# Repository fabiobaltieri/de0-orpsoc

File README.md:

DE0 ORPSoC
==========

This project is an addon I/O board for the Altera DE0-Nano.  It is meant to
be used as a development platform for the OpenRISC soft CPU.

The peripherals on the board are:

* Dual USB to UART
* RMII Ethernet
* SPI Ethernet
* RTC w/ battery backup (I2C)
* Thermal sensor (I2C)
* Micro SD card
* USB 1.1 Transceiver
* Reset button
* Status LEDs

All devices are powered at 3.3V from the DE0 regulators, though a set of
jumpers allow to power the DE0 itself from one of the USB ports of the I/O
board.

License
-------

This work is licensed under a Creative Commons Attribution-ShareAlike 3.0
License.

Contents
--------

    README      this file
    hardware/   source directory for the hardware design

Hardware
--------

All hardware files (schematic, layout and libraries) are in CadSoft Eagle
format.

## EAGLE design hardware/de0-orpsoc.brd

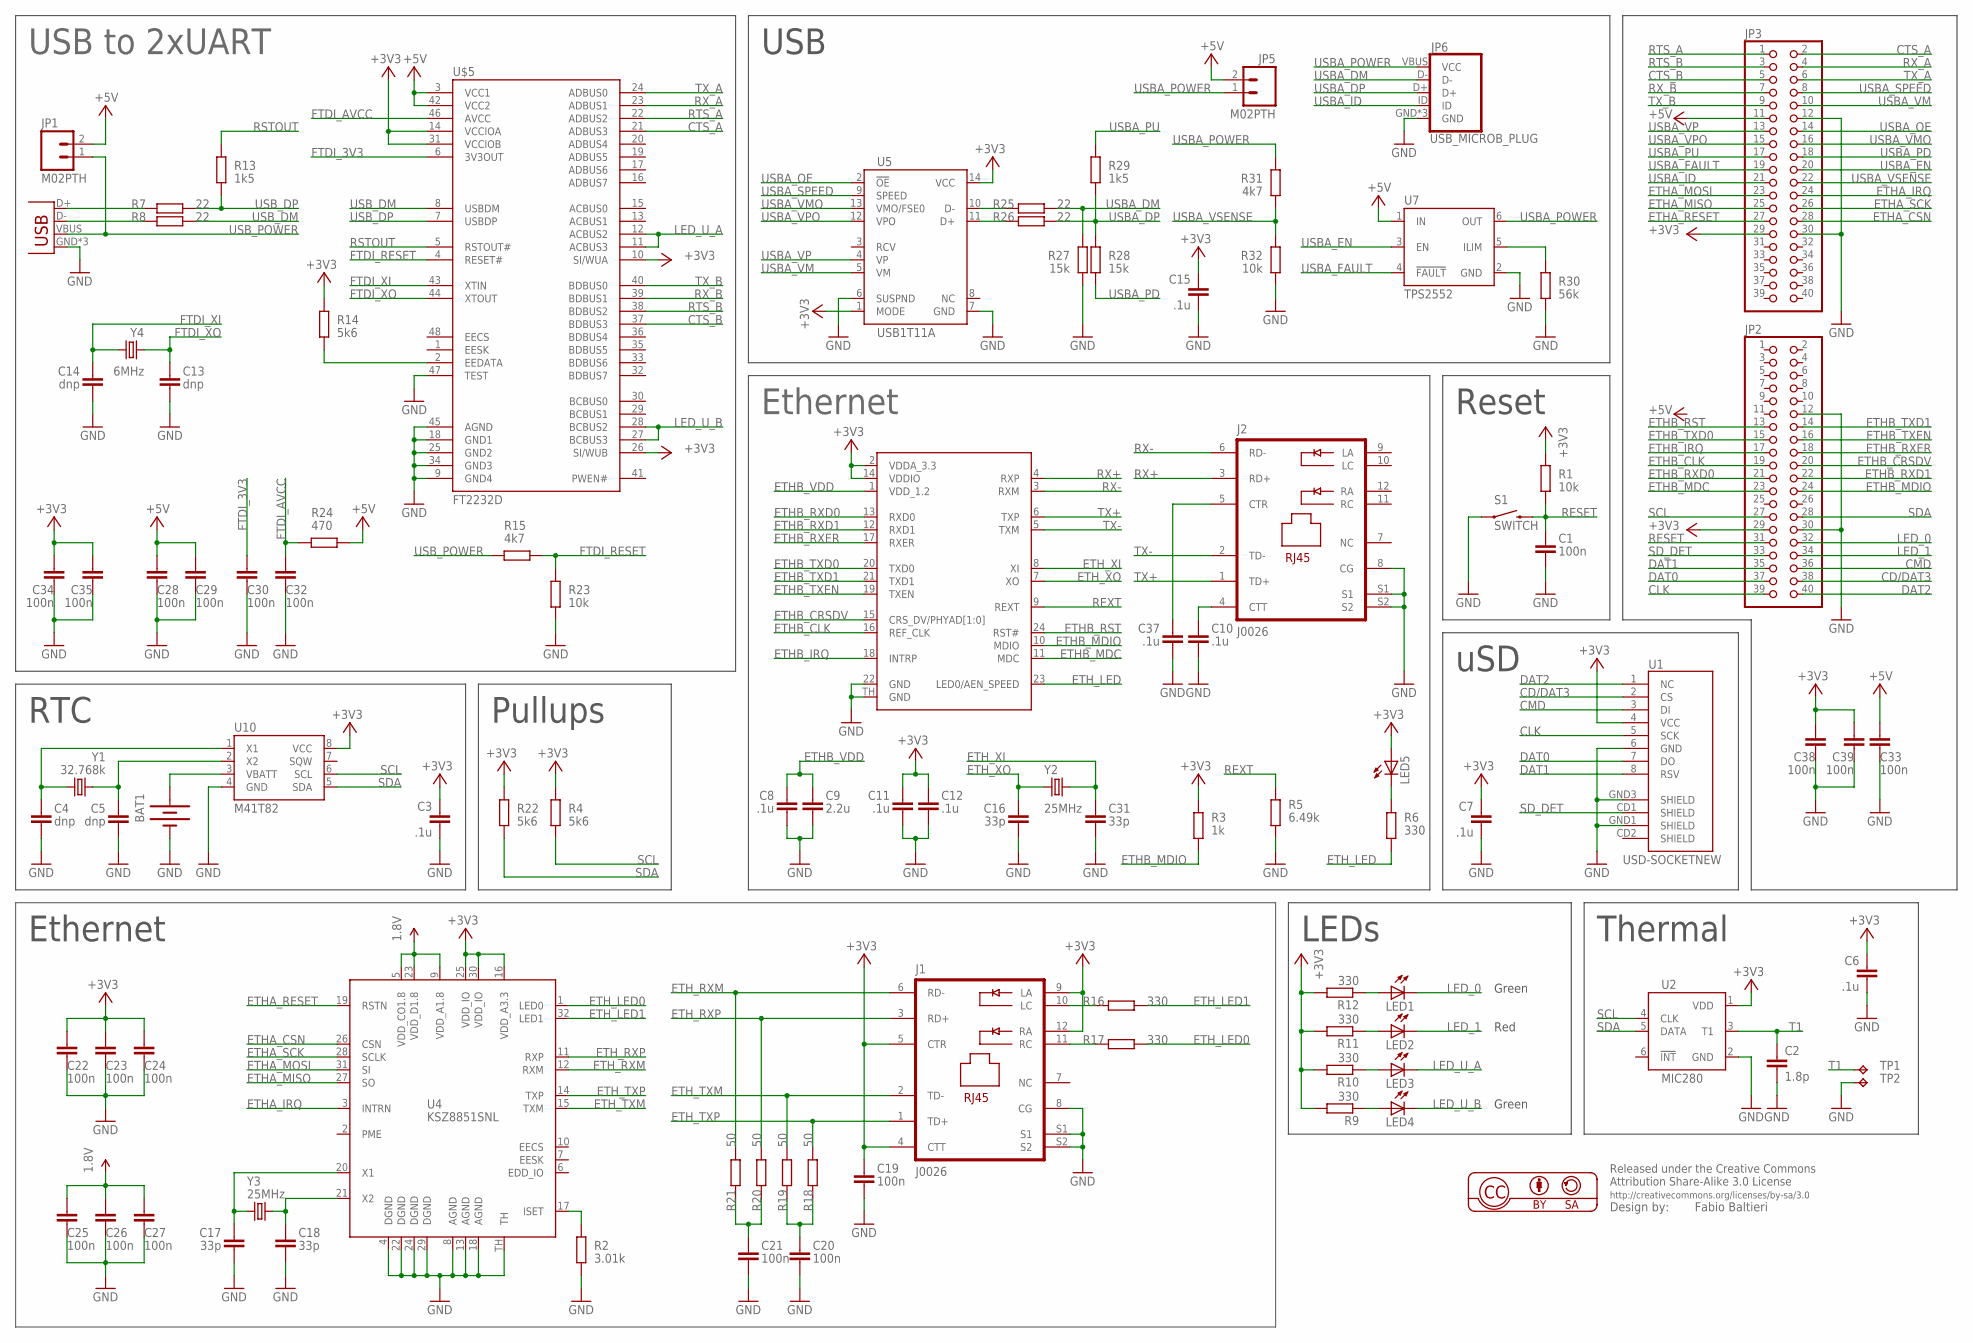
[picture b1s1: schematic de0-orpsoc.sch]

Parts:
BAT1: BATTERY12PTH; BATTCON_12MM_PTH
C1, C19, C20, C21, C22, C23, C24, C25, C26, C27, C28, C29, C30, C32, C33, C34, C35, C38, C39: 100n; C0603
C2: 1.8p; C0603
C3, C6, C7, C8, C10, C11, C12, C15, C37: .1u; C0603
C4, C5, C13, C14: dnp; C0603
C9: 2.2u; C0603
C16, C17, C18, C31: 33p; C0603
J1, J2: J0026; PJ-J0
JP1, JP5: M02PTH; 1X02
JP2, JP3: PINHD-2X20; 2X20
JP6: USB_MICROB_PLUG; USB-MICROB
JP10: USB-MICROB
LED1, LED2, LED3, LED4, LED5: LEDCHIPLED_0805; CHIPLED_0805
R1, R23, R32: 10k; R0603
R2: 3.01k; R0603
R3: 1k; R0603
R4, R14, R22: 5k6; R0603
R5: 6.49k; R0603
R6, R9, R10, R11, R12, R16, R17: 330; R0603
R7, R8, R25, R26: 22; R0603
R13, R29: 1k5; R0603
R15, R31: 4k7; R0603
R18, R19, R20, R21: 50; R0603
R24: 470; R0603
R27, R28: 15k; R0603
R30: 56k; R0603
S1: SWITCH; TACTILE_SWITCH_SMD
TP1, TP2: TPTP12R; TP12R
U1: USD-SOCKETNEW; MICRO-SD-SOCKET-PP
U2: MIC280; SOT23-6L
U3: KSZ8081RNA; QFN24
U4: KSZ8851SNL; MLF32-TH
U5: USB1T11A; SOIC14
U7: TPS2552; SOT23-6L
U10: M41T82; SO08
U$5: FT2232D; LQFP-48
Y1: 32.768k; CRYSTAL-32KHZ-SMD
Y2, Y3: 25MHz; CRYSTAL-SMD-5X3
Y4: 6MHz; CRYSTAL-SMD-5X3

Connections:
1.8V: C25.1, C26.1, C27.1, U4.5 (VDD_CO1.8), U4.9 (VDD_A1.8), U4.23 (VDD_D1.8)
+3V3: C3.1, C6.1, C7.1, C11.1, C12.1, C15.1, C19.1, C22.1, C23.1, C24.1, C34.1, C35.1, C38.1, C39.1, J1.4 (CTT), J1.5 (CTR), J1.9 (LA), J1.12 (RA), JP2.29, JP3.29, LED5.A, R1.2, R3.2, R4.1, R9.2, R10.2, R11.2, R12.2, R14.1, R22.1, U1.4 (VCC), U2.1 (VDD), U3.2 (VDDA_3.3), U3.14 (VDDIO), U4.16 (VDD_A3.3), U4.25 (VDD_IO), U4.30 (VDD_IO), U5.1 (MODE), U5.14 (VCC), U10.8 (VCC), U$5.10 (SI/WUA), U$5.14 (VCCIOA), U$5.26 (SI/WUB), U$5.31 (VCCIOB)
+5V: C28.1, C29.1, C33.1, JP1.2, JP3.11, JP5.2, R24.2, U7.1 (IN), U$5.3 (VCC1), U$5.42 (VCC2)
CD/DAT3: JP2.38, U1.2 (CS)
CLK: JP2.39, U1.5 (SCK)
CMD: JP2.36, U1.3 (DI)
CTS_A: JP3.2, U$5.21 (ADBUS3)
CTS_B: JP3.5, U$5.37 (BDBUS3)
DAT0: JP2.37, U1.7 (DO)
DAT1: JP2.35, U1.8 (RSV)
DAT2: JP2.40, U1.1 (NC)
ETHA_CSN: JP3.28, U4.26 (CSN)
ETHA_IRQ: JP3.24, U4.3 (INTRN)
ETHA_MISO: JP3.25, U4.27 (SO)
ETHA_MOSI: JP3.23, U4.31 (SI)
ETHA_RESET: JP3.27, U4.19 (RSTN)
ETHA_SCK: JP3.26, U4.28 (SCLK)
ETHB_CLK: JP2.19, U3.16 (REF_CLK)
ETHB_CRSDV: JP2.20, U3.15 (CRS_DV/PHYAD[1:0])
ETHB_IRQ: JP2.17, U3.18 (INTRP)
ETHB_MDC: JP2.23, U3.11 (MDC)
ETHB_MDIO: JP2.24, R3.1, U3.10 (MDIO)
ETHB_RST: JP2.13, U3.24 (RST#)
ETHB_RXD0: JP2.21, U3.13 (RXD0)
ETHB_RXD1: JP2.22, U3.12 (RXD1)
ETHB_RXER: JP2.18, U3.17 (RXER)
ETHB_TXD0: JP2.15, U3.20 (TXD0)
ETHB_TXD1: JP2.14, U3.21 (TXD1)
ETHB_TXEN: JP2.16, U3.19 (TXEN)
ETHB_VDD: C8.1, C9.1, U3.1 (VDD_1.2)
ETH_LED: R6.1, U3.23 (LED0/AEN_SPEED)
ETH_LED0: R17.2, U4.1 (LED0)
ETH_LED1: R16.2, U4.32 (LED1)
ETH_RXM: J1.6 (RD-), R21.2, U4.12 (RXM)
ETH_RXP: J1.3 (RD+), R20.2, U4.11 (RXP)
ETH_TXM: J1.2 (TD-), R19.2, U4.15 (TXM)
ETH_TXP: J1.1 (TD+), R18.2, U4.14 (TXP)
ETH_XI: C31.1, U3.8 (XI), Y2.3 (2)
ETH_XO: C16.1, U3.7 (XO), Y2.1
FTDI_3V3: C30.1, U$5.6 (3V3OUT)
FTDI_AVCC: C32.1, R24.1, U$5.46 (AVCC)
FTDI_RESET: R15.2, R23.1, U$5.4 (RESET#)
FTDI_XI: C14.1, U$5.43 (XTIN), Y4.3 (2)
FTDI_XO: C13.1, U$5.44 (XTOUT), Y4.1
GND: BAT1.GND (-), C1.2, C2.2, C3.2, C4.2, C5.2, C6.2, C7.2, C8.2, C9.2, C10.2, C11.2, C12.2, C13.2, C14.2, C15.2, C16.2, C17.2, C18.2, C19.2, C20.2, C21.2, C22.2, C23.2, C24.2, C25.2, C26.2, C27.2, C28.2, C29.2, C30.2, C31.2, C32.2, C33.2, C34.2, C35.2, C37.2, C38.2, C39.2, J1.8 (CG), J1.S1, J1.S2, J2.8 (CG), J2.S1, J2.S2, JP2.12, JP2.30, JP3.12, JP3.30, JP6.GND, JP6.MT1 (GND), JP6.MT2 (GND), JP10.GND, JP10.MT1 (GND), JP10.MT2 (GND), R2.2, R5.1, R23.2, R27.2, R30.2, R32.2, S1.1, TP2.TP, U1.6 (GND), U1.GND1 (SHIELD), U1.GND3 (SHIELD), U2.2 (GND), U3.22 (GND), U3.TH (GND), U4.4 (DGND), U4.8 (AGND), U4.13 (AGND), U4.18 (AGND), U4.22 (DGND), U4.24 (DGND), U4.29 (DGND), U4.TH, U5.6 (SUSPND), U5.7 (GND), U7.2 (GND), U10.4 (GND), U$5.9 (GND4), U$5.18 (GND1), U$5.25 (GND2), U$5.34 (GND3), U$5.45 (AGND), U$5.47 (TEST)
LED_0: JP2.32, LED1.C
LED_1: JP2.34, LED2.C
LED_U_A: LED3.C, U$5.11 (ACBUS3), U$5.12 (ACBUS2)
LED_U_B: LED4.C, U$5.27 (BCBUS3), U$5.28 (BCBUS2)
unnamed: LED3.A, R10.1
unnamed: LED4.A, R9.1
unnamed: C5.1, U10.2 (X2), Y1.X1 (1)
unnamed: BAT1.VCC@1 (+), U10.3 (VBATT)
unnamed: C4.1, U10.1 (X1), Y1.X2 (2)
unnamed: LED5.C, R6.2
unnamed: JP10.D-, R8.1
unnamed: C10.1, J2.4 (CTT)
unnamed: C37.1, J2.5 (CTR)
unnamed: R25.1, U5.10 (D-)
unnamed: JP10.D+, R7.1
unnamed: R26.1, U5.11 (D+)
unnamed: R14.2, U$5.2 (EEDATA)
unnamed: R30.1, U7.5 (ILIM)
unnamed: LED1.A, R12.1
unnamed: LED2.A, R11.1
unnamed: J1.10 (LC), R16.1
unnamed: J1.11 (RC), R17.1
unnamed: R2.1, U4.17 (ISET)
unnamed: C17.1, U4.20 (X1), Y3.1
unnamed: C18.1, U4.21 (X2), Y3.3 (2)
unnamed: C21.1, R20.1, R21.1
unnamed: C20.1, R18.1, R19.1
RESET: C1.1, JP2.31, R1.1, S1.3 (2)
REXT: R5.2, U3.9 (REXT)
RSTOUT: R13.1, U$5.5 (RSTOUT#)
RTS_A: JP3.1, U$5.22 (ADBUS2)
RTS_B: JP3.3, U$5.38 (BDBUS2)
RX+: J2.3 (RD+), U3.4 (RXP)
RX-: J2.6 (RD-), U3.3 (RXM)
RX_A: JP3.4, U$5.23 (ADBUS1)
RX_B: JP3.7, U$5.39 (BDBUS1)
SCL: JP2.27, R4.2, U2.4 (CLK), U10.6 (SCL)
SDA: JP2.28, R22.2, U2.5 (DATA), U10.5 (SDA)
SD_DET: JP2.33, U1.CD1 (SHIELD)
T1: C2.1, TP1.TP, U2.3 (T1)
TX+: J2.1 (TD+), U3.6 (TXP)
TX-: J2.2 (TD-), U3.5 (TXM)
TX_A: JP3.6, U$5.24 (ADBUS0)
TX_B: JP3.9, U$5.40 (BDBUS0)
USBA_DM: JP6.D-, R25.2, R27.1
USBA_DP: JP6.D+, R26.2, R28.1, R29.2
USBA_EN: JP3.20, U7.3 (EN)
USBA_FAULT: JP3.19, U7.4 (!FAULT)
USBA_ID: JP3.21, JP6.ID
USBA_OE: JP3.14, U5.2 (!OE)
USBA_PD: JP3.18, R28.2
USBA_POWER: JP5.1, JP6.VBUS (VCC), R31.1, U7.6 (OUT)
USBA_PU: JP3.17, R29.1
USBA_SPEED: JP3.8, U5.9 (SPEED)
USBA_VM: JP3.10, U5.5 (VM)
USBA_VMO: JP3.16, U5.13 (VMO/FSE0)
USBA_VP: JP3.13, U5.4 (VP)
USBA_VPO: JP3.15, U5.12 (VPO)
USBA_VSENSE: JP3.22, R31.2, R32.1
USB_DM: R8.2, U$5.8 (USBDM)
USB_DP: R7.2, R13.2, U$5.7 (USBDP)
USB_POWER: JP1.1, JP10.VBUS, R15.1

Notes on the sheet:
Ethernet
Reset
LEDs
RTC
Pullups
Thermal
USB to 2xUART
uSD
USB
Red
Green
Green

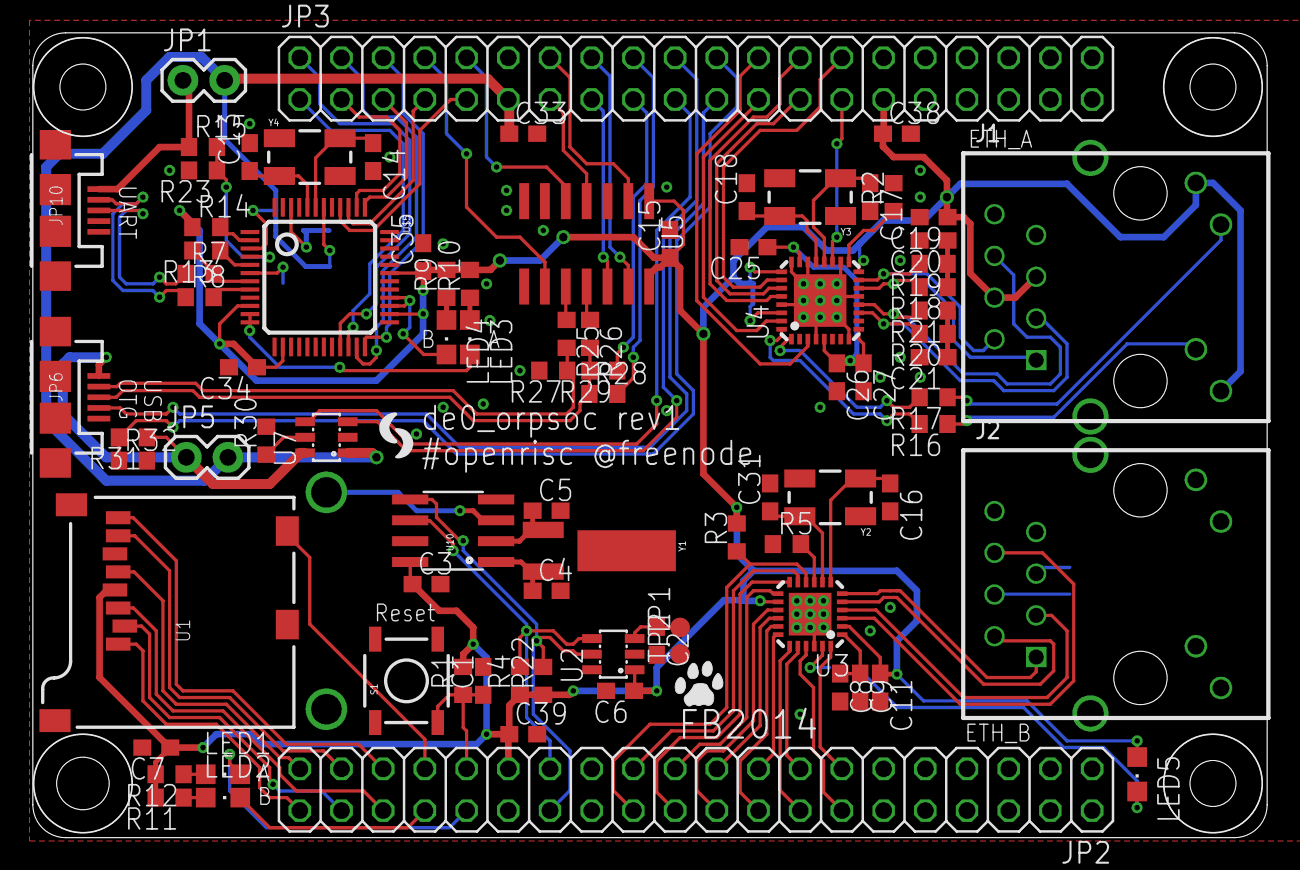
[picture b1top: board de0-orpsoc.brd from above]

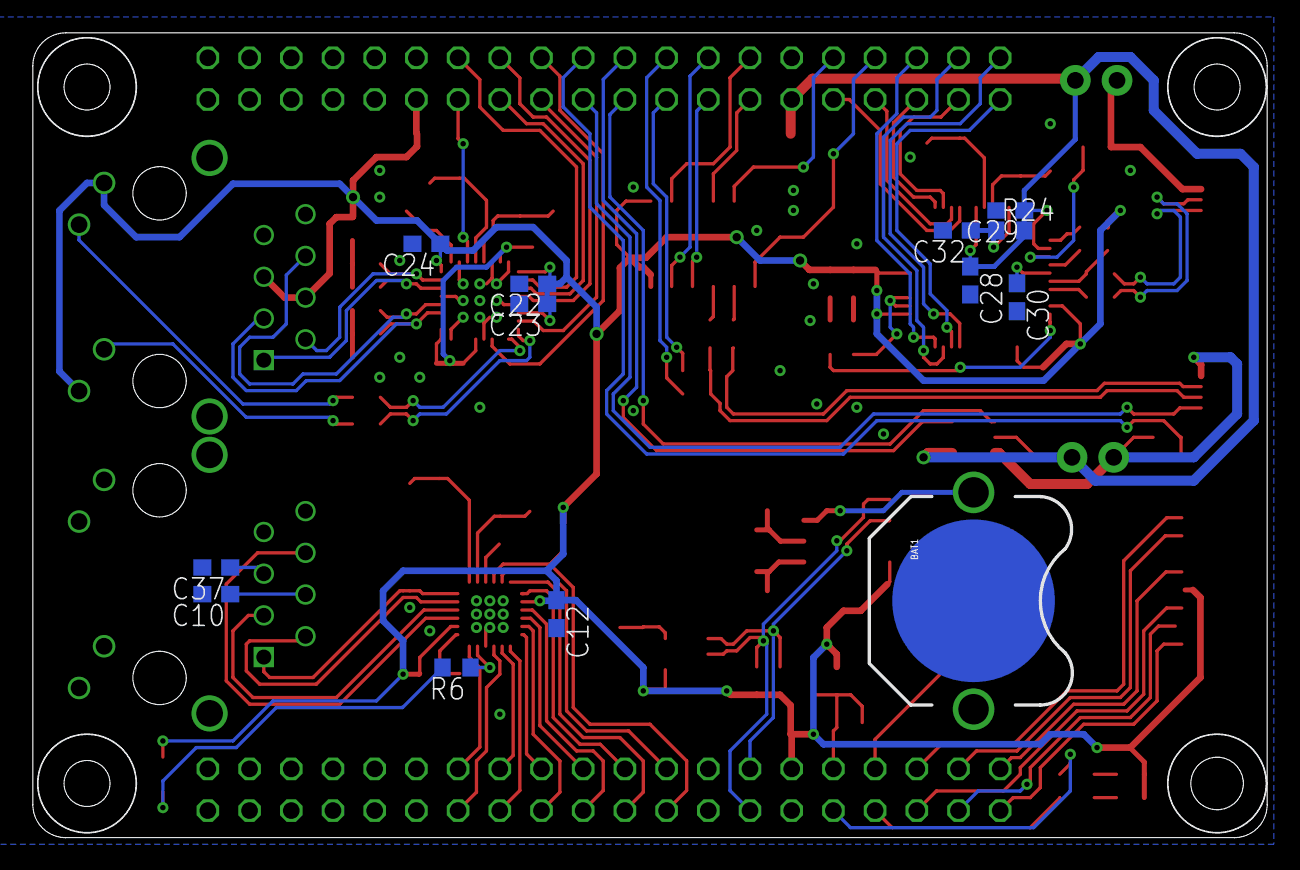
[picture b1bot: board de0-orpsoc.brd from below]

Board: 2 copper layers, 75.2 x 49.0 mm, 101 parts (13 on the bottom side), 107 nets.

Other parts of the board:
U$1: CAT-L
U$4: CS

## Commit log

2014-03-29 rev1
2014-03-29 hw: fix osc cap value
2014-03-29 hw: mark a yellow LED
2014-03-30 hw: misc value fixes
2014-03-30 Add README file
2014-04-12 hw: part values tweaks
2014-04-12 hw: change rtc pn

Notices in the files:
parts and their libraries:
SparkFun-Connectors: Licensing: CC v3.0 Share-Alike You are welcome to use this library for commercial purposes.
balto: Released under the Creative Commons
balto: http://creativecommons.org/licenses/by-sa/3.0
